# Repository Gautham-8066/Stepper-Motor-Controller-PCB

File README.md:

# Stepper-Motor-Controller-PCB
This board allows users to drive a stepper motor using a microcontroller, incorporating limit switch detection for homing and end-stop functionality. It is ideal for CNC machines, 3D printers, robotics, and automation projects.                                                                                                                          

Schematic:

3D view of the board

Don't mind the limit switch placement on the PCB, I know it can't be used if its placed there, but I don't know another way to show it in 3D view instead of placing on the PCB.
I think you may Understand :)

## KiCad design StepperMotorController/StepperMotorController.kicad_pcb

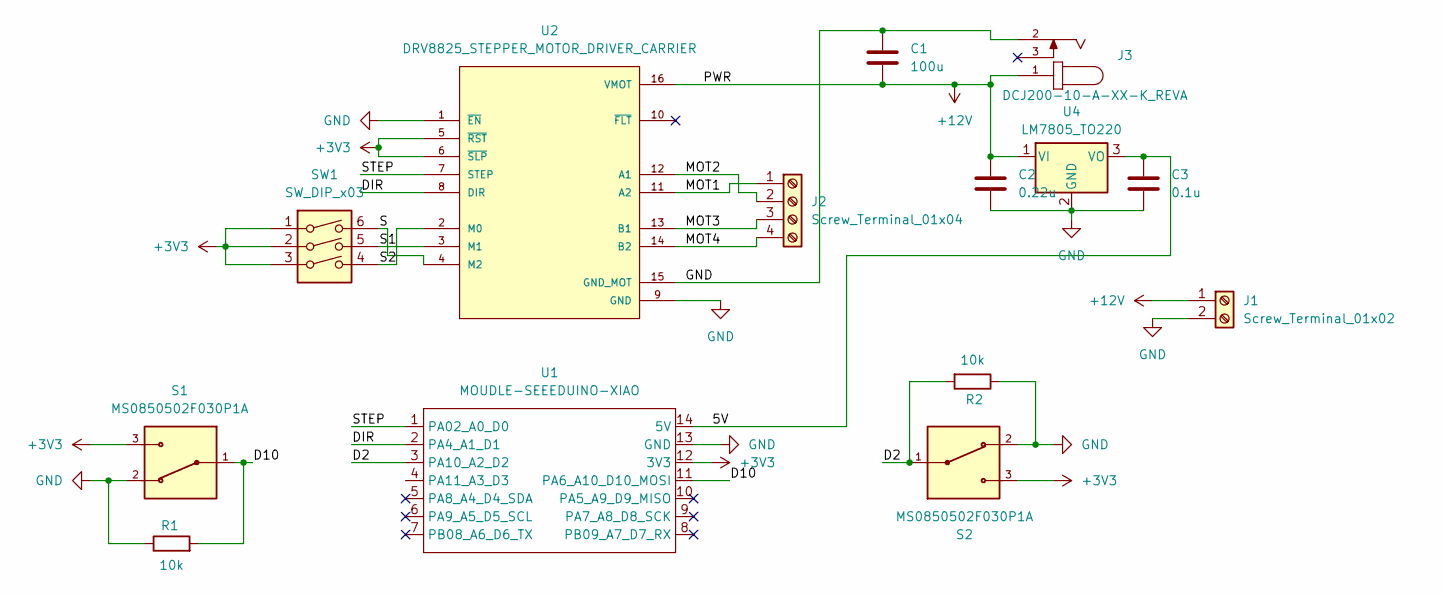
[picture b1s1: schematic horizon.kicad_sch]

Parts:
C1: 100u; C_0402_1005Metric_Pad0.74x0.62mm_HandSolder
C2: 0.22u; C_0402_1005Metric_Pad0.74x0.62mm_HandSolder
C3: 0.1u; C_0402_1005Metric_Pad0.74x0.62mm_HandSolder
J1: Screw_Terminal_01x02; TerminalBlock_4Ucon_1x02_P3.50mm_Horizontal
J2: Screw_Terminal_01x04; TerminalBlock_4Ucon_1x04_P3.50mm_Horizontal
J3: DCJ200-10-A-XX-K_REVA; GCT_DCJ200-10-A-XX-K_REVA; PARTREV A
R1, R2: 10k; R_0201_0603Metric
S1, S2: MS0850502F030P1A; SW_MS0850502F030P1A
SW1: SW_DIP_x03; SW_DIP_SPSTx03_Slide_6.7x9.18mm_W6.73mm_P2.54mm_LowProfile_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
U1: MOUDLE-SEEEDUINO-XIAO; MOUDLE14P-2.54-21X17.8MM
U2: DRV8825_STEPPER_MOTOR_DRIVER_CARRIER; IC_DRV8825_STEPPER_MOTOR_DRIVER_CARRIER
U4: LM7805_TO220; TO-220-3_Vertical

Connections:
+3V3: S1.3, S2.3, SW1.1, SW1.2, SW1.3, U1.12 (3V3), U2.5 (~RST), U2.6 (~SLP)
+12V: C1.2, C2.1, J1.1, J3.1, U2.16 (VMOT), U4.1 (VI)
/5V: C3.1, U1.14 (5V), U4.3 (VO)
/D2: R2.2, S2.1, U1.3 (PA10_A2_D2)
/D10: R1.2, S1.1, U1.11 (PA6_A10_D10_MOSI)
/DIR: U1.2 (PA4_A1_D1), U2.8 (DIR)
/MOT1: J2.1, U2.11 (A2)
/MOT2: J2.2, U2.12 (A1)
/MOT3: J2.3, U2.13 (B1)
/MOT4: J2.4, U2.14 (B2)
/S: SW1.6, U2.4 (M2)
/S1: SW1.5, U2.3 (M1)
/S2: SW1.4, U2.2 (M0)
/STEP: U1.1 (PA02_A0_D0), U2.7 (STEP)
GND: C1.1, C2.2, C3.2, J1.2, J3.2, R1.1, R2.1, S1.2, S2.2, U1.13 (GND), U2.1 (~EN), U2.9 (GND), U2.15 (GND_MOT), U4.2 (GND)

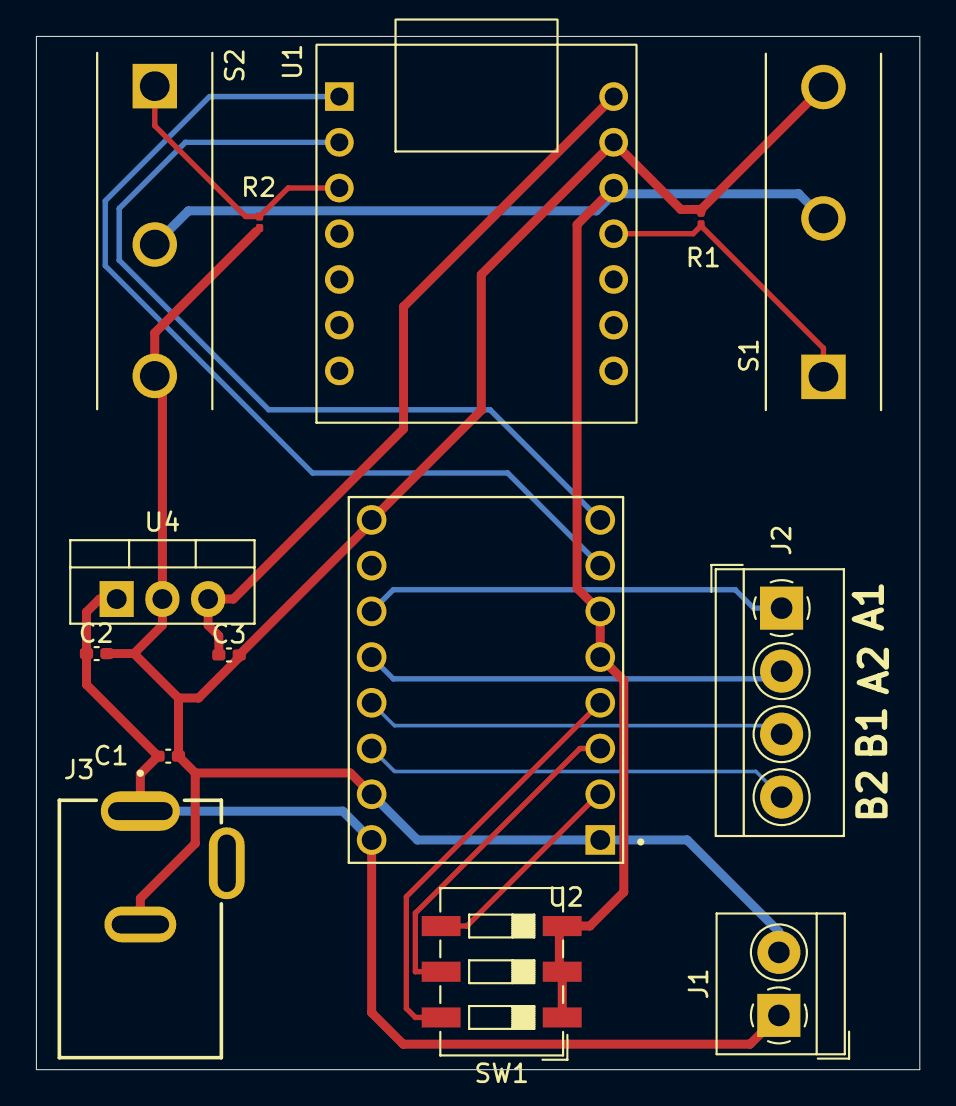
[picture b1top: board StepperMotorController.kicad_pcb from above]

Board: 2 copper layers, 49.1 x 57.4 mm, 14 parts (0 on the bottom side), 15 nets.

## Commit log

2025-03-14 Create SMC-PCB
2025-03-14 3D view of the Board
    Don't mind the limit switch placement on the PCB, I know it can't be used if its placed there, but I don't know another way to show it in 3D view instead of placing on the PCB.
    I think you may Understand :)
2025-03-17 Update LICENSE
